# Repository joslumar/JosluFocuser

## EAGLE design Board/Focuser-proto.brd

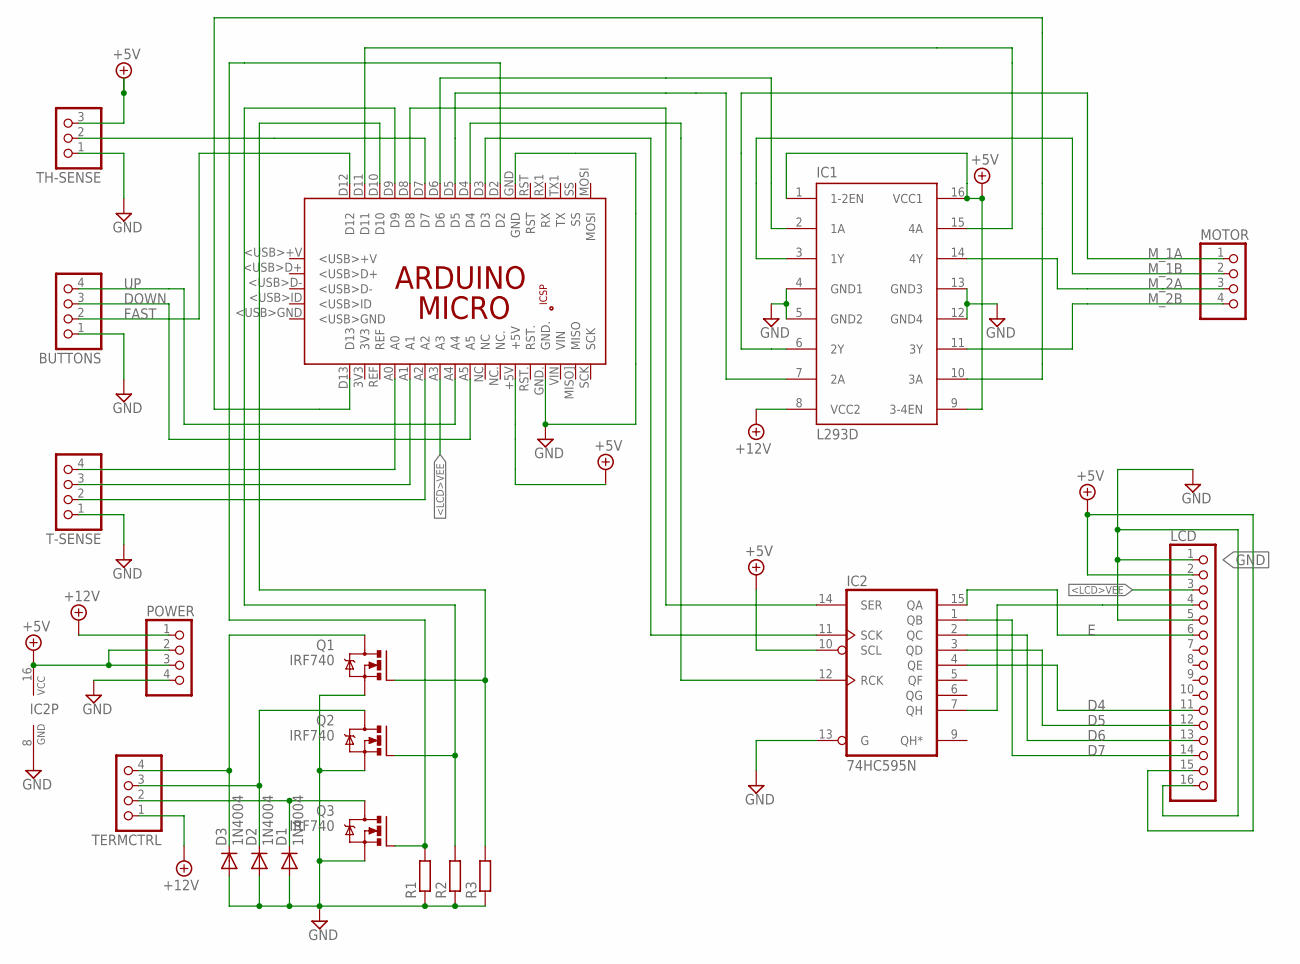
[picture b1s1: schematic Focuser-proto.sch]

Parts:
BUTTONS: PINHD-1X4; 1X04
D1, D2, D3: 1N4004; DO41-10
IC1: L293D; DIL16
IC2: 74HC595N; DIL16
LCD: PINHD-1X16; 1X16
MOTOR: PINHD-1X4; 1X04
PCB1: ARDUINO_MICRO
POWER: PINHD-1X4; 1X04
Q1, Q2, Q3: IRF740; TO220BV
R1, R2, R3: R-EU_0207/7; 0207/7
T-SENSE: PINHD-1X4; 1X04
TERMCTRL: PINHD-1X4; 1X04
TH-SENSE: PINHD-1X3; 1X03

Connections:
+5V: IC1.1 (1-2EN), IC1.9 (3-4EN), IC1.16 (VCC1), IC2.10 (SCL), IC2.16 (VCC), LCD.2, LCD.15, PCB1.+5V, POWER.2, POWER.3, TH-SENSE.3
+12V: IC1.8 (VCC2), POWER.1, TERMCTRL.1
<LCD>VEE: LCD.3, PCB1.A3
D4: IC2.4 (QE), LCD.11
D5: IC2.3 (QD), LCD.12
D6: IC2.2 (QC), LCD.13
D7: IC2.1 (QB), LCD.14
DOWN: BUTTONS.3, PCB1.A5
E: IC2.15 (QA), LCD.6
FAST: BUTTONS.2, PCB1.D12
GND: BUTTONS.1, D1.A, D2.A, D3.A, IC1.4 (GND1), IC1.5 (GND2), IC1.12 (GND4), IC1.13 (GND3), IC2.8 (GND), IC2.13 (G), LCD.1, LCD.5, LCD.16, PCB1.GND, PCB1.GND., POWER.4, Q1.S, Q2.S, Q3.S, R1.1, R2.1, R3.1, T-SENSE.1, TH-SENSE.1
M_1A: IC1.6 (2Y), MOTOR.1
M_1B: IC1.3 (1Y), MOTOR.2
M_2A: IC1.14 (4Y), MOTOR.3
M_2B: IC1.11 (3Y), MOTOR.4
unnamed: PCB1.A2, T-SENSE.2
unnamed: PCB1.A0, T-SENSE.4
unnamed: PCB1.A1, T-SENSE.3
unnamed: D1.C, Q3.D, TERMCTRL.2
unnamed: D2.C, Q2.D, TERMCTRL.3
unnamed: D3.C, Q1.D, TERMCTRL.4
unnamed: PCB1.D2, Q3.G, R1.2
unnamed: IC2.11 (SCK), PCB1.D3
unnamed: IC1.2 (1A), PCB1.D6
unnamed: IC1.7 (2A), PCB1.D5
unnamed: IC1.15 (4A), PCB1.D11
unnamed: IC1.10 (3A), PCB1.D13
unnamed: PCB1.D7, TH-SENSE.2
unnamed: IC2.12 (RCK), PCB1.D4
unnamed: IC2.14 (SER), PCB1.D8
unnamed: IC2.7 (QH), LCD.4
unnamed: PCB1.D9, Q2.G, R2.2
unnamed: PCB1.D10, Q1.G, R3.2
UP: BUTTONS.4, PCB1.A4

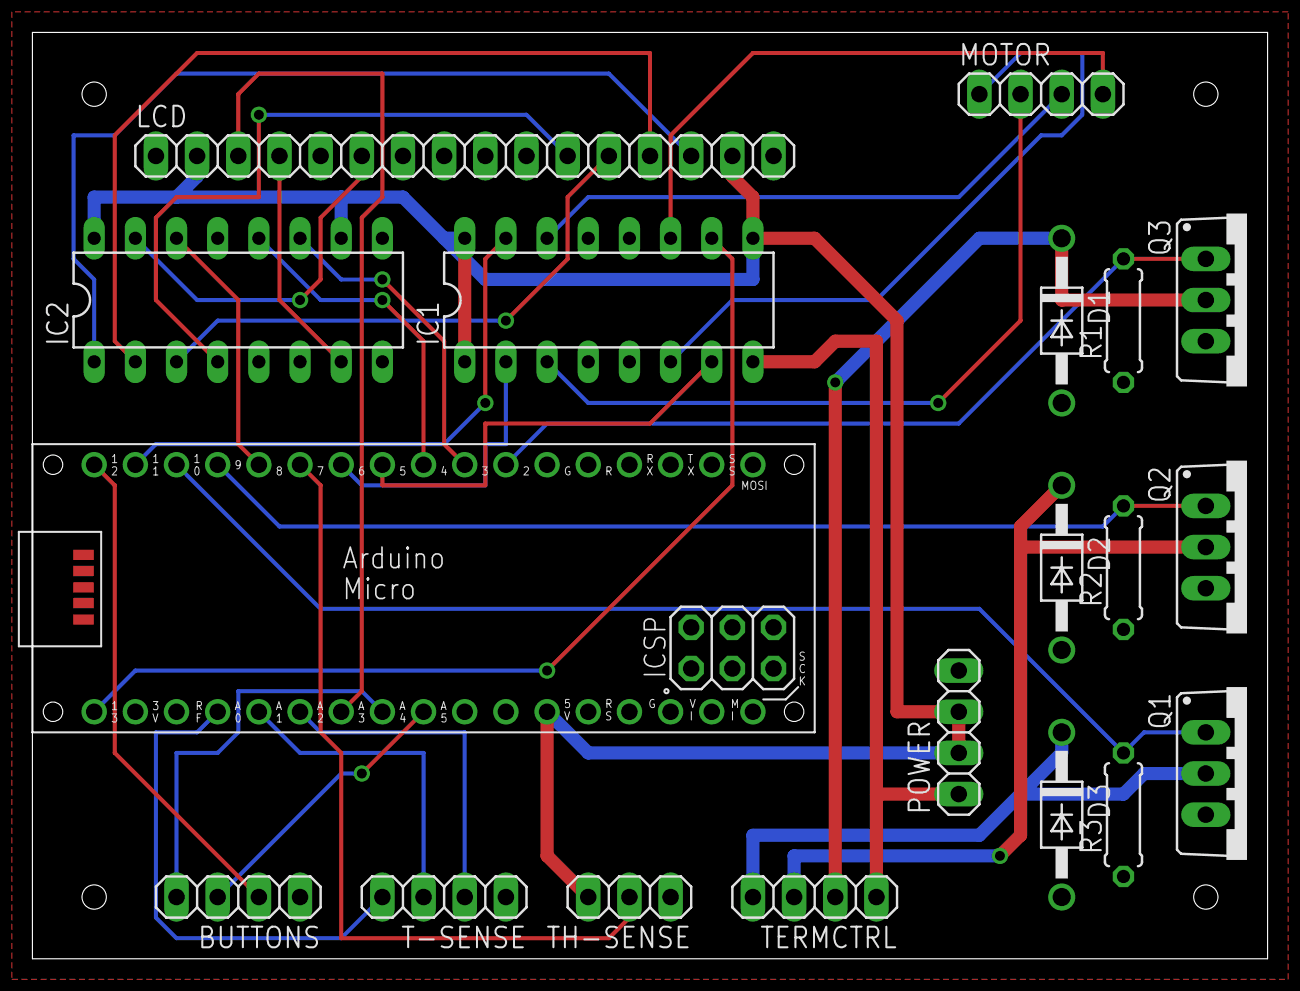
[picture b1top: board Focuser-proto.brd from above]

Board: 2 copper layers, 76.2 x 57.2 mm, 19 parts (0 on the bottom side), 34 nets.

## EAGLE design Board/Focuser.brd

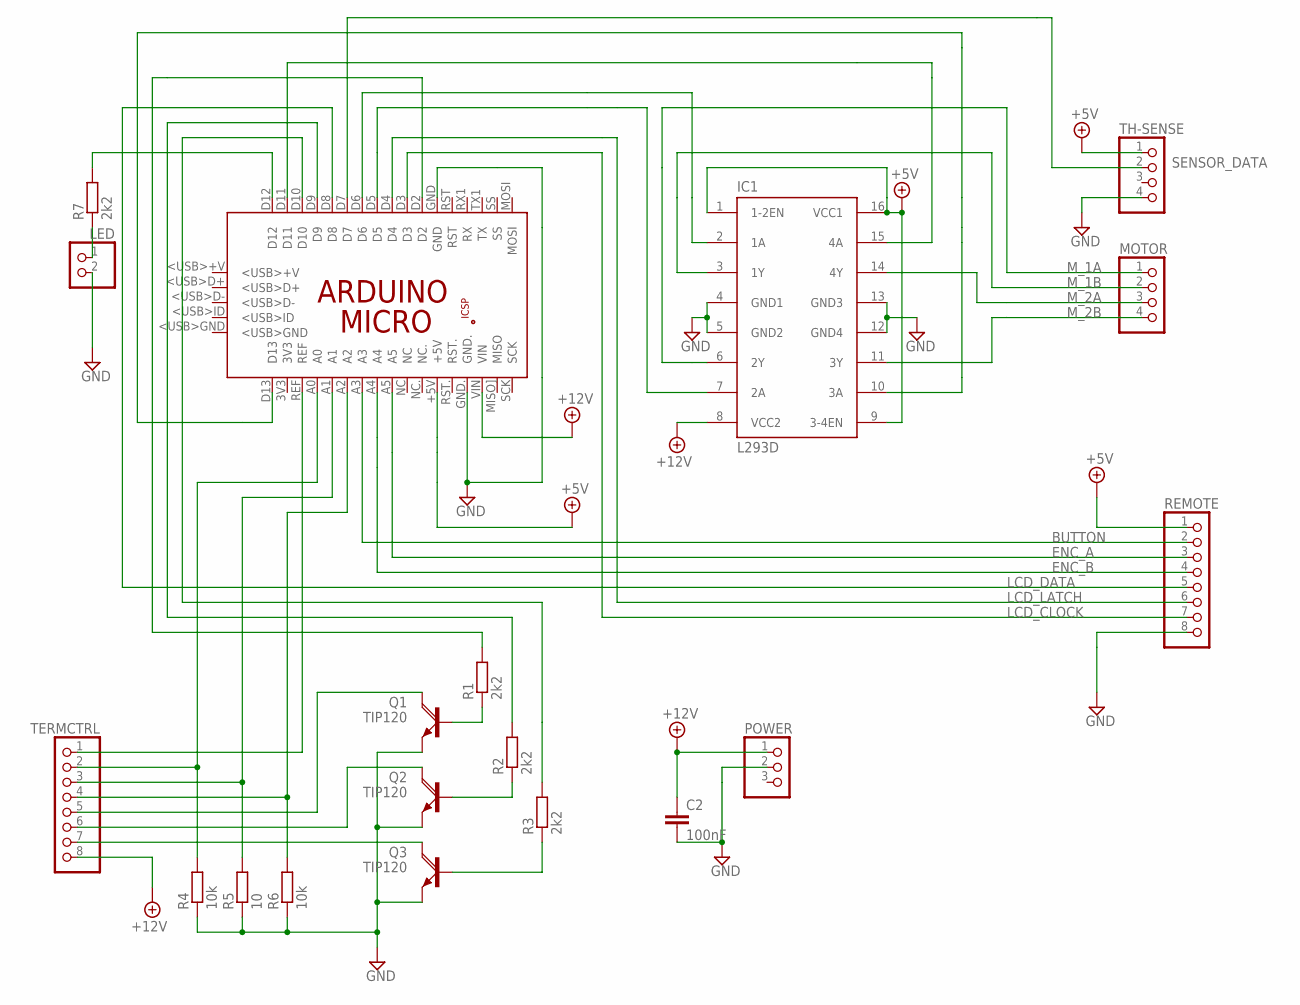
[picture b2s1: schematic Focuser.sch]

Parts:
C2: 100nF; C025_050-025X075
IC1: L293D; DIL16
LED: PINHD-1X2; 1X02
MOTOR: PINHD-1X4; 1X04
PCB1: ARDUINO_MICRO
POWER: PINHD-1X3; 1X03
Q1, Q2, Q3: TIP120; TO220AH
R1, R2, R3, R7: 2k2; 0207/7
R4, R6: 10k; 0207/7
R5: 10; 0207/7
REMOTE: PINHD-1X8; 1X08
TERMCTRL: PINHD-1X8; 1X08
TH-SENSE: PINHD-1X4; 1X04

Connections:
+5V: IC1.1 (1-2EN), IC1.9 (3-4EN), IC1.16 (VCC1), PCB1.+5V, REMOTE.1, TH-SENSE.1
+12V: C2.1, IC1.8 (VCC2), PCB1.VIN, POWER.1, TERMCTRL.8
BUTTON: PCB1.A3, REMOTE.2
ENC_A: PCB1.A5, REMOTE.3
ENC_B: PCB1.A4, REMOTE.4
GND: C2.2, IC1.4 (GND1), IC1.5 (GND2), IC1.12 (GND4), IC1.13 (GND3), LED.2, PCB1.GND, PCB1.GND., POWER.2, Q1.E, Q2.E, Q3.E, R4.1, R5.1, R6.1, REMOTE.8, TH-SENSE.4
LCD_CLOCK: PCB1.D3, REMOTE.7
LCD_DATA: PCB1.D8, REMOTE.5
LCD_LATCH: PCB1.D4, REMOTE.6
M_1A: IC1.6 (2Y), MOTOR.1
M_1B: IC1.3 (1Y), MOTOR.2
M_2A: IC1.14 (4Y), MOTOR.3
M_2B: IC1.11 (3Y), MOTOR.4
unnamed: PCB1.A2, R6.2, TERMCTRL.4
unnamed: PCB1.A0, R4.2, TERMCTRL.2
unnamed: PCB1.A1, R5.2, TERMCTRL.3
unnamed: Q3.C, TERMCTRL.7
unnamed: Q2.C, TERMCTRL.6
unnamed: Q1.C, TERMCTRL.5
unnamed: PCB1.D2, R1.2
unnamed: IC1.2 (1A), PCB1.D6
unnamed: IC1.7 (2A), PCB1.D5
unnamed: IC1.15 (4A), PCB1.D11
unnamed: LED.1, R7.1
unnamed: IC1.10 (3A), PCB1.D13
unnamed: PCB1.D12, R7.2
unnamed: Q3.B, R3.1
unnamed: Q2.B, R2.1
unnamed: Q1.B, R1.1
unnamed: PCB1.D9, R2.2
unnamed: PCB1.D10, R3.2
unnamed: PCB1.REF, TERMCTRL.1
SENSOR_DATA: PCB1.D7, TH-SENSE.2

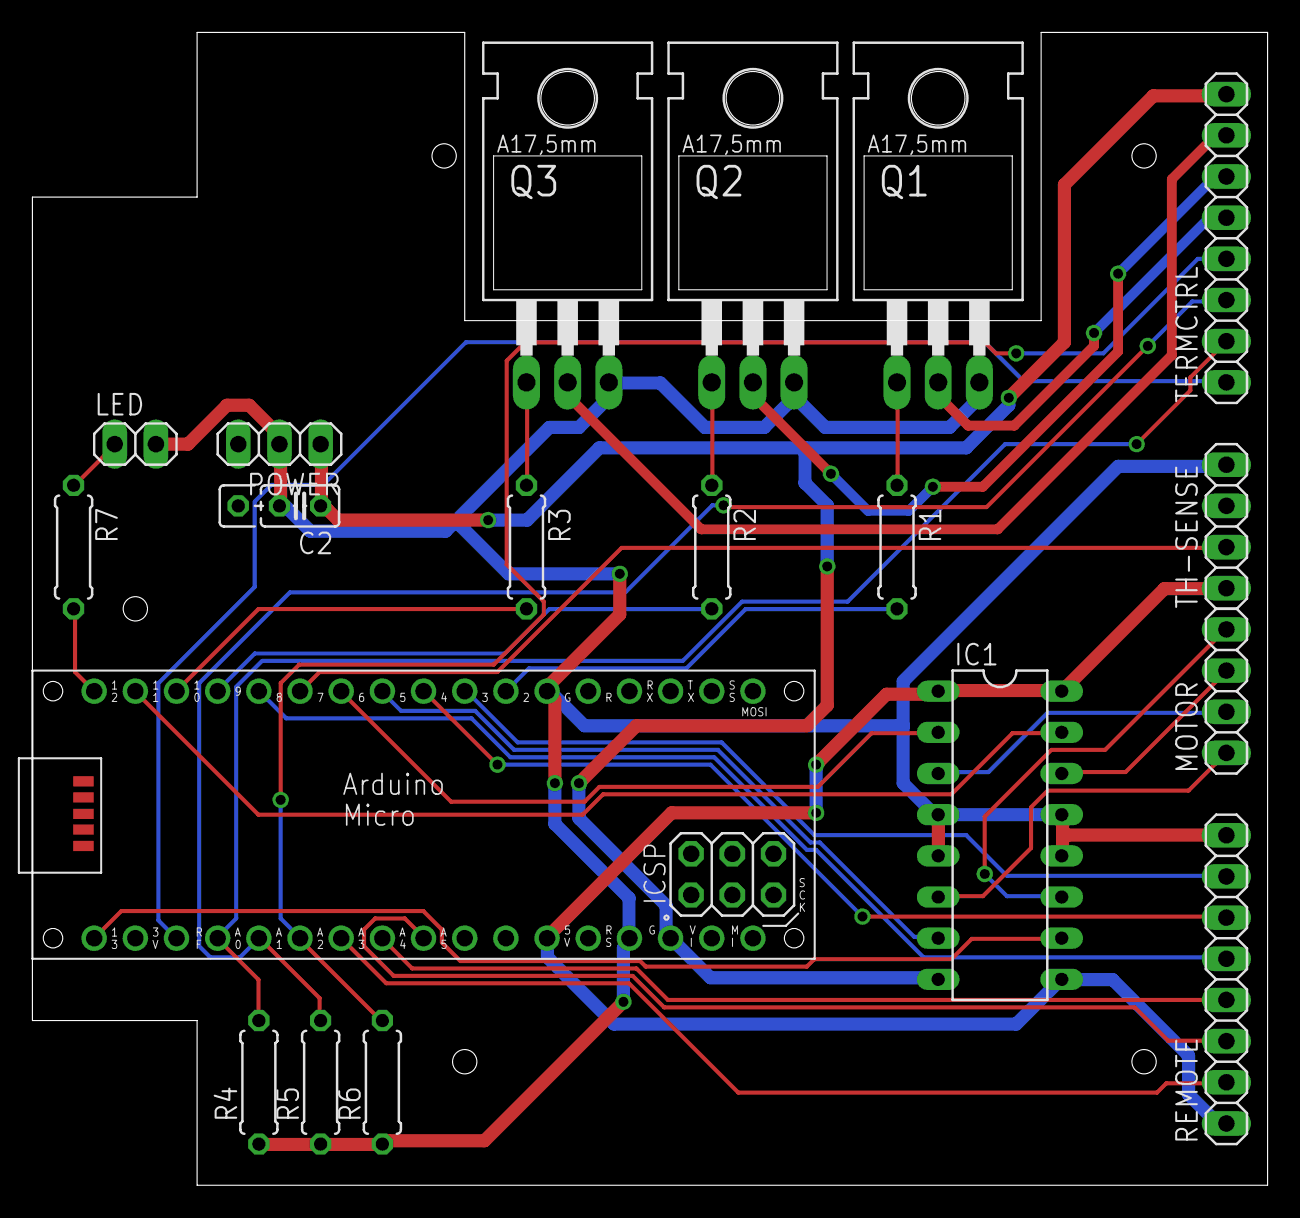
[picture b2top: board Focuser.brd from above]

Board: 2 copper layers, 76.2 x 71.1 mm, 19 parts (0 on the bottom side), 33 nets.

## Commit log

2017-05-20 First
2017-05-20 new file: Board/Focuser-proto.brd new file: Board/Focuser-proto.sch new file: Board/Focuser.brd new file: Board/Focuser.sch
2017-05-20 renamed: Focuser.h -> JosluFocuser/JosluFocuser.h renamed: Focuser_v13.ino -> JosluFocuser/JosluFocuser.ino deleted: Board/Focuser-base.brd
2017-05-20 new file: indi/CMakeLists.txt new file: indi/cmake_modules/FindINDI.cmake new file: indi/config.h.cmake new file: indi/joslufocus.cpp new file: indi/joslufocus.h new file: indi/joslufocus.xml.cmake d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
2017-05-20 deleted: Board/Focuser-base.brd
2018-02-18 Version 13 - rearrage code and some trasnlations
2018-02-18 V13 - rearrage code and some trasnlations
2018-02-19 V14 - Rearrange code and some translations
2019-11-23 Minor changes
